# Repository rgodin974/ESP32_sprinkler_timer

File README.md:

# ESP32_sprinkler_timer

Sprinkler timer designed for ESP32.

Coded on PlateformIO and VS Code. Project based on RitonDuino : https://riton-duino.blogspot.com/2023/08/esp32-micro-irrigation-connectee-partie.html

Add few features :
- waterings every days
- waterings even days
- waterings odd days
- waterings custom days
- seasonal adjustment
- enable/disable watering(s)

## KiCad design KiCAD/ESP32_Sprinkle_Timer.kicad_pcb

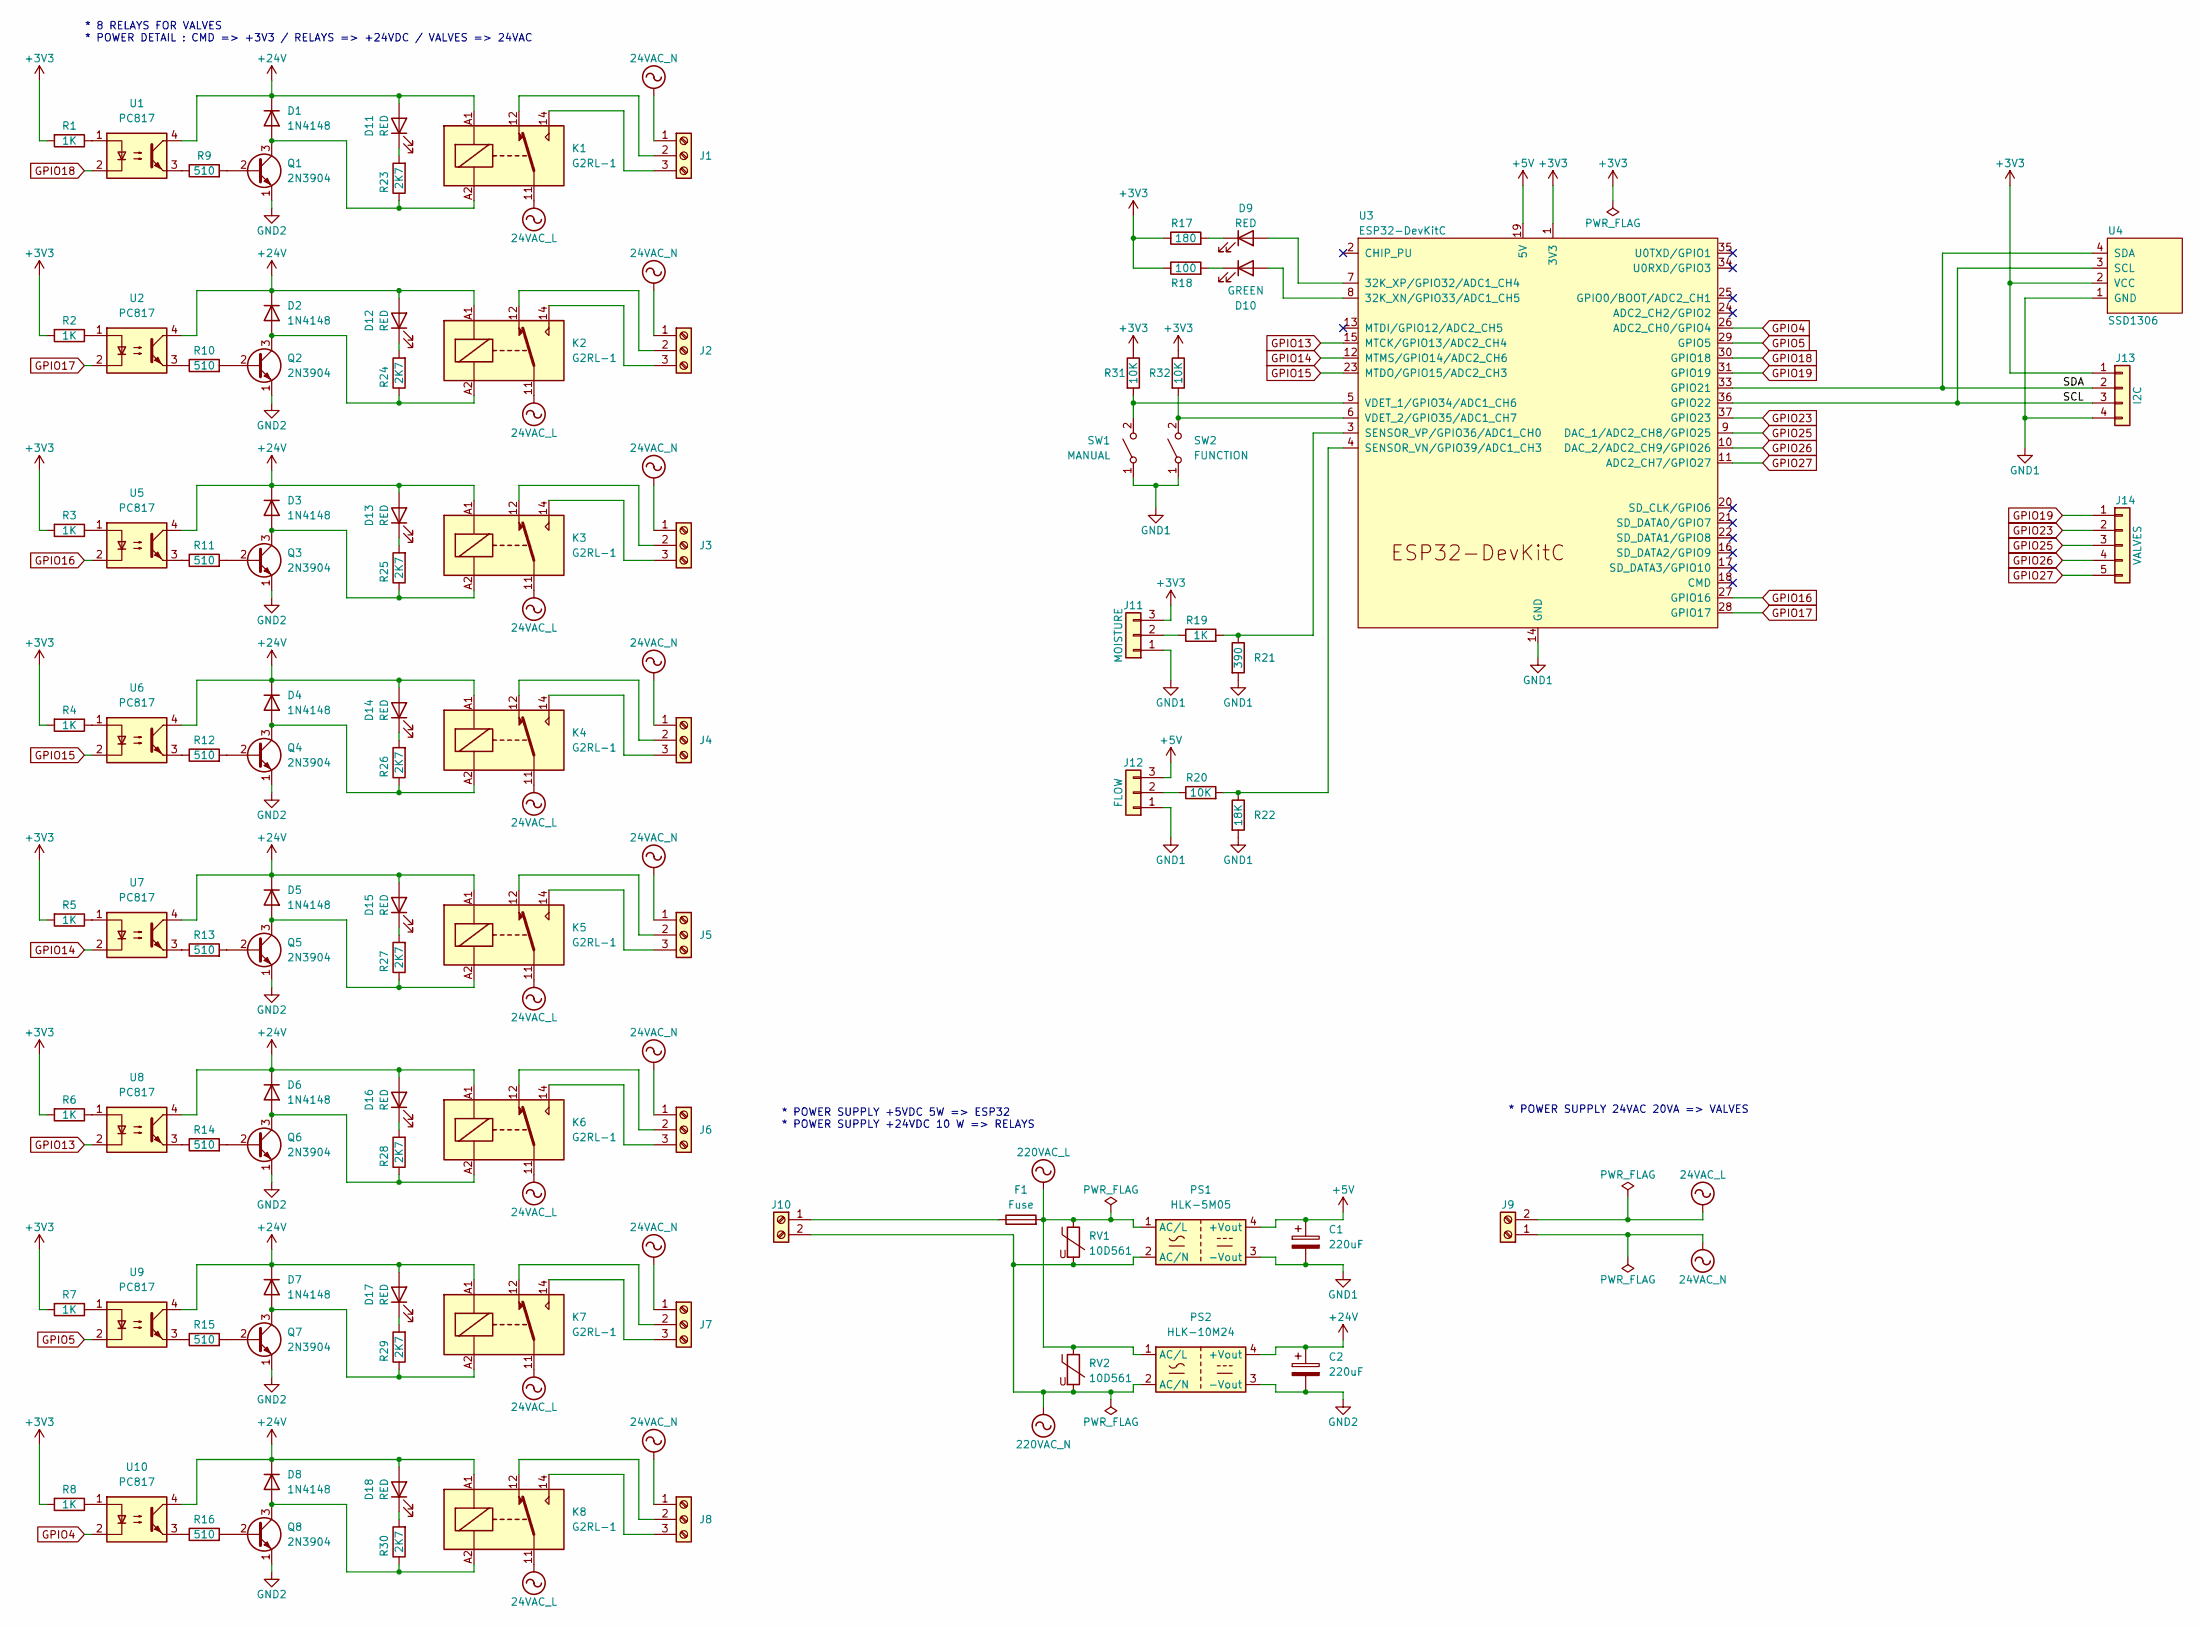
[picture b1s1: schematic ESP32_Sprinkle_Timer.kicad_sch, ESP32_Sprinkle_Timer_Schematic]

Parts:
C1: 220uF; CP_Radial_D8.0mm_P3.50mm
C2: 220uF; CP_Radial_D10.0mm_P5.00mm
D1, D2, D3, D4, D5, D6, D7, D8: 1N4148; D_DO-35_SOD27_P7.62mm_Horizontal
D9, D11, D12, D13, D14, D15, D16, D17, D18: RED; LED_D3.0mm
D10: GREEN; LED_D3.0mm
F1: Fuse; Fuseholder_Cylinder-5x20mm_Schurter_0031_8201_Horizontal_Op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
J1, J2, J3, J4, J5, J6, J7, J8: Screw_Terminal_01x03; TerminalBlock_bornier-3_P5.08mm
J9, J10: Screw_Terminal_01x02; TerminalBlock_bornier-2_P5.08mm
J11: MOISTURE; PinHeader_1x03_P2.54mm_Horizontal
J12: FLOW; PinHeader_1x03_P2.54mm_Horizontal
J13: I2C; PinHeader_1x04_P2.54mm_Vertical
J14: VALVES; PinHeader_1x05_P2.54mm_Vertical
K1, K2, K3, K4, K5, K6, K7, K8: G2RL-1; Relay_SPDT_Omron_G2RL-1
PS1: HLK-5M05; Converter_ACDC_HiLink_HLK-5Mxx
PS2: HLK-10M24; Converter_ACDC_HiLink_HLK-10Mxx
Q1, Q2, Q3, Q4, Q5, Q6, Q7, Q8: 2N3904; TO-92_Inline_Wide
R1, R2, R3, R4, R5, R6, R7, R8, R19: 1K; R_Axial_DIN0207_L6.3mm_D2.5mm_P7.62mm_Horizontal
R9, R10, R11, R12, R13, R14, R15, R16: 510; R_Axial_DIN0207_L6.3mm_D2.5mm_P7.62mm_Horizontal
R17: 180; R_Axial_DIN0207_L6.3mm_D2.5mm_P7.62mm_Horizontal
R18: 100; R_Axial_DIN0207_L6.3mm_D2.5mm_P7.62mm_Horizontal
R20, R31, R32: 10K; R_Axial_DIN0207_L6.3mm_D2.5mm_P7.62mm_Horizontal
R21: 390; R_Axial_DIN0207_L6.3mm_D2.5mm_P7.62mm_Horizontal
R22: 18K; R_Axial_DIN0207_L6.3mm_D2.5mm_P7.62mm_Horizontal
R23, R24, R25, R26, R27, R28, R29, R30: 2K7; R_Axial_DIN0207_L6.3mm_D2.5mm_P7.62mm_Horizontal
RV1, RV2: 10D561; RV_Disc_D12mm_W7.5mm_P7.5mm
SW1: MANUAL; SW_PUSH-12mm
SW2: FUNCTION; SW_PUSH-12mm
U1, U2, U5, U6, U7, U8, U9, U10: PC817; DIP-4_W7.62mm
U3: ESP32-DevKitC
U4: SSD1306; SSD1306_0.96_Oled

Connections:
24VAC_L: J9.2, K1.11, K2.11, K3.11, K4.11, K5.11, K6.11, K7.11, K8.11
24VAC_N: J1.1, J2.1, J3.1, J4.1, J5.1, J6.1, J7.1, J8.1, J9.1
220VAC_L: F1.2, PS1.1 (AC/L), PS2.1 (AC/L), RV1.1, RV2.1
220VAC_N: J10.2, PS1.2 (AC/N), PS2.2 (AC/N), RV1.2, RV2.2
+3V3: J11.3, J13.1, R1.2, R2.2, R3.2, R4.2, R5.2, R6.2, R7.2, R8.2, R17.1, R18.1, R31.1, R32.1, U3.1 (3V3), U4.2 (VCC)
+5V: C1.1, J12.3, PS1.4 (+Vout), U3.19 (5V)
+24V: C2.1, D1.1 (K), D2.1 (K), D3.1 (K), D4.1 (K), D5.1 (K), D6.1 (K), D7.1 (K), D8.1 (K), D11.2 (A), D12.2 (A), D13.2 (A), D14.2 (A), D15.2 (A), D16.2 (A), D17.2 (A), D18.2 (A), K1.A1, K2.A1, K3.A1, K4.A1, K5.A1, K6.A1, K7.A1, K8.A1, PS2.4 (+Vout), U1.4, U2.4, U5.4, U6.4, U7.4, U8.4, U9.4, U10.4
/SCL: J13.3, U3.36 (GPIO22), U4.3 (SCL)
/SDA: J13.2, U3.33 (GPIO21), U4.4 (SDA)
GND1: C1.2, J11.1, J12.1, J13.4, PS1.3 (-Vout), R21.2, R22.2, SW1.1 (A), SW2.1 (A), U3.14 (GND), U3.32 (GND), U3.38 (GND), U4.1 (GND)
GND2: C2.2, PS2.3 (-Vout), Q1.1 (E), Q2.1 (E), Q3.1 (E), Q4.1 (E), Q5.1 (E), Q6.1 (E), Q7.1 (E), Q8.1 (E)
GPIO4: U3.26 (ADC2_CH0/GPIO4), U10.2
GPIO5: U3.29 (GPIO5), U9.2
GPIO13: U3.15 (MTCK/GPIO13/ADC2_CH4), U8.2
GPIO14: U3.12 (MTMS/GPIO14/ADC2_CH6), U7.2
GPIO15: U3.23 (MTDO/GPIO15/ADC2_CH3), U6.2
GPIO16: U3.27 (GPIO16), U5.2
GPIO17: U2.2, U3.28 (GPIO17)
GPIO18: U1.2, U3.30 (GPIO18)
GPIO19: J14.1, U3.31 (GPIO19)
GPIO23: J14.2, U3.37 (GPIO23)
GPIO25: J14.3, U3.9 (DAC_1/ADC2_CH8/GPIO25)
GPIO26: J14.4, U3.10 (DAC_2/ADC2_CH9/GPIO26)
GPIO27: J14.5, U3.11 (ADC2_CH7/GPIO27)
unnamed: D1.2 (A), K1.A2, Q1.3 (C), R23.1
unnamed: D2.2 (A), K2.A2, Q2.3 (C), R24.1
unnamed: D3.2 (A), K3.A2, Q3.3 (C), R25.1
unnamed: D4.2 (A), K4.A2, Q4.3 (C), R26.1
unnamed: D5.2 (A), K5.A2, Q5.3 (C), R27.1
unnamed: D6.2 (A), K6.A2, Q6.3 (C), R28.1
unnamed: D7.2 (A), K7.A2, Q7.3 (C), R29.1
unnamed: D8.2 (A), K8.A2, Q8.3 (C), R30.1
unnamed: D9.2 (A), U3.7 (32K_XP/GPIO32/ADC1_CH4)
unnamed: D9.1 (K), R17.2
unnamed: D10.2 (A), U3.8 (32K_XN/GPIO33/ADC1_CH5)
unnamed: D10.1 (K), R18.2
unnamed: D11.1 (K), R23.2
unnamed: D12.1 (K), R24.2
unnamed: D13.1 (K), R25.2
unnamed: D14.1 (K), R26.2
unnamed: D15.1 (K), R27.2
unnamed: D16.1 (K), R28.2
unnamed: D17.1 (K), R29.2
unnamed: D18.1 (K), R30.2
unnamed: J1.2, K1.12
unnamed: J1.3, K1.14
unnamed: J2.2, K2.12
unnamed: J2.3, K2.14
unnamed: J3.2, K3.12
unnamed: J3.3, K3.14
unnamed: J4.2, K4.12
unnamed: J4.3, K4.14
unnamed: J5.2, K5.12
unnamed: J5.3, K5.14
unnamed: J6.2, K6.12
unnamed: J6.3, K6.14
unnamed: J7.2, K7.12
unnamed: J7.3, K7.14
unnamed: J8.2, K8.12
unnamed: J8.3, K8.14
unnamed: F1.1, J10.1
unnamed: J11.2, R19.1
unnamed: J12.2, R20.1
unnamed: Q1.2 (B), R9.2
unnamed: Q2.2 (B), R10.2
unnamed: Q3.2 (B), R11.2
unnamed: Q4.2 (B), R12.2
unnamed: Q5.2 (B), R13.2
unnamed: Q6.2 (B), R14.2
unnamed: Q7.2 (B), R15.2
unnamed: Q8.2 (B), R16.2
unnamed: R1.1, U1.1
unnamed: R2.1, U2.1
unnamed: R3.1, U5.1
unnamed: R4.1, U6.1
unnamed: R5.1, U7.1
unnamed: R6.1, U8.1
unnamed: R7.1, U9.1
unnamed: R8.1, U10.1
unnamed: R9.1, U1.3
unnamed: R10.1, U2.3
unnamed: R11.1, U5.3
unnamed: R12.1, U6.3
unnamed: R13.1, U7.3
unnamed: R14.1, U8.3
unnamed: R15.1, U9.3
unnamed: R16.1, U10.3
unnamed: R31.2, SW1.2 (B), U3.5 (VDET_1/GPIO34/ADC1_CH6)
unnamed: R32.2, SW2.2 (B), U3.6 (VDET_2/GPIO35/ADC1_CH7)
unnamed: R20.2, R22.1, U3.4 (SENSOR_VN/GPIO39/ADC1_CH3)
unnamed: R19.2, R21.1, U3.3 (SENSOR_VP/GPIO36/ADC1_CH0)

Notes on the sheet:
* POWER SUPPLY +5VDC 5W => ESP32 * POWER SUPPLY +24VDC 10 W => RELAYS
* 8 RELAYS FOR VALVES * POWER DETAIL : CMD => +3V3 / RELAYS => +24VDC / VALVES => 24VAC
* POWER SUPPLY 24VAC 20VA => VALVES

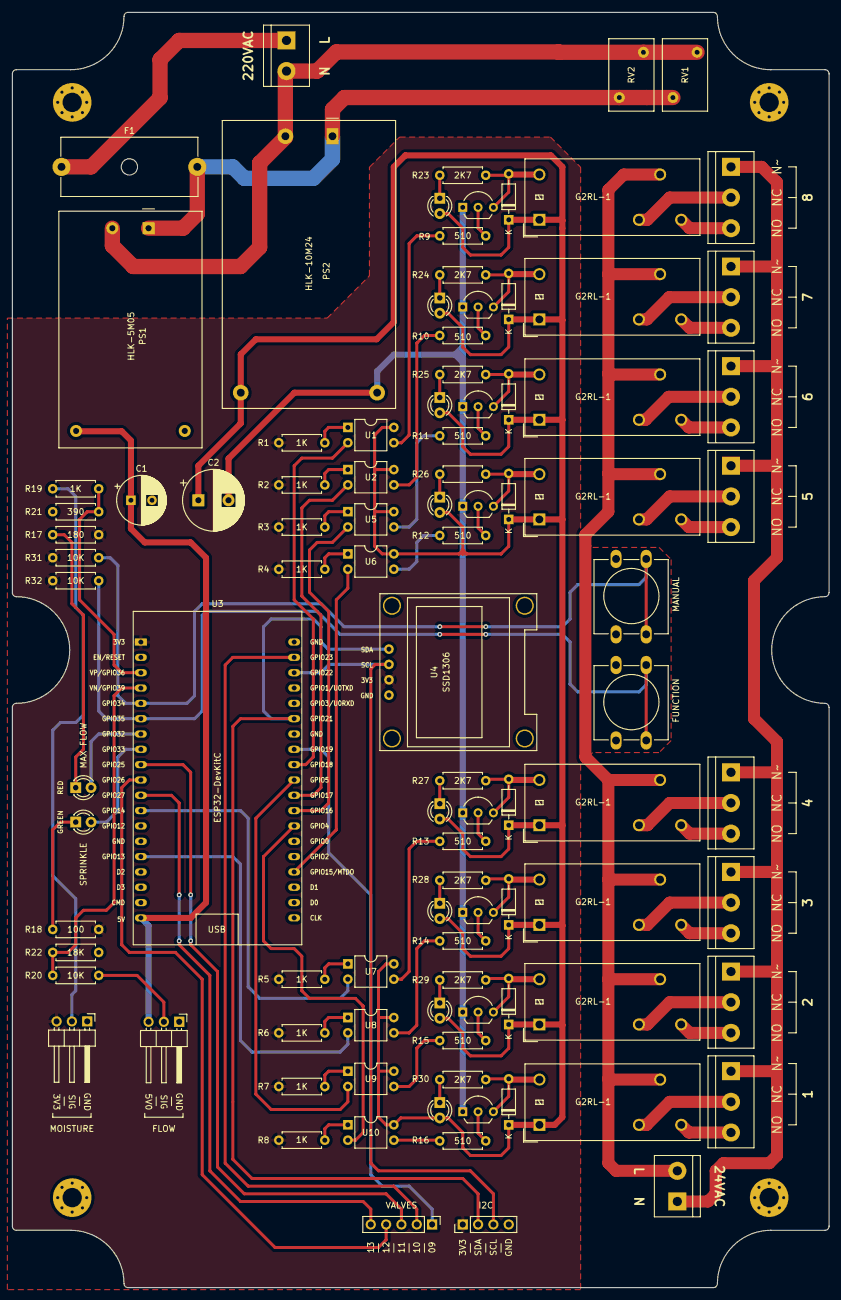
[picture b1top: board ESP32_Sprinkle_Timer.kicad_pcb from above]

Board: 2 copper layers, 135.3 x 211.3 mm, 99 parts (0 on the bottom side), 91 nets.

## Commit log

2024-05-24 Update files
2024-05-24 Add KiCAD files
